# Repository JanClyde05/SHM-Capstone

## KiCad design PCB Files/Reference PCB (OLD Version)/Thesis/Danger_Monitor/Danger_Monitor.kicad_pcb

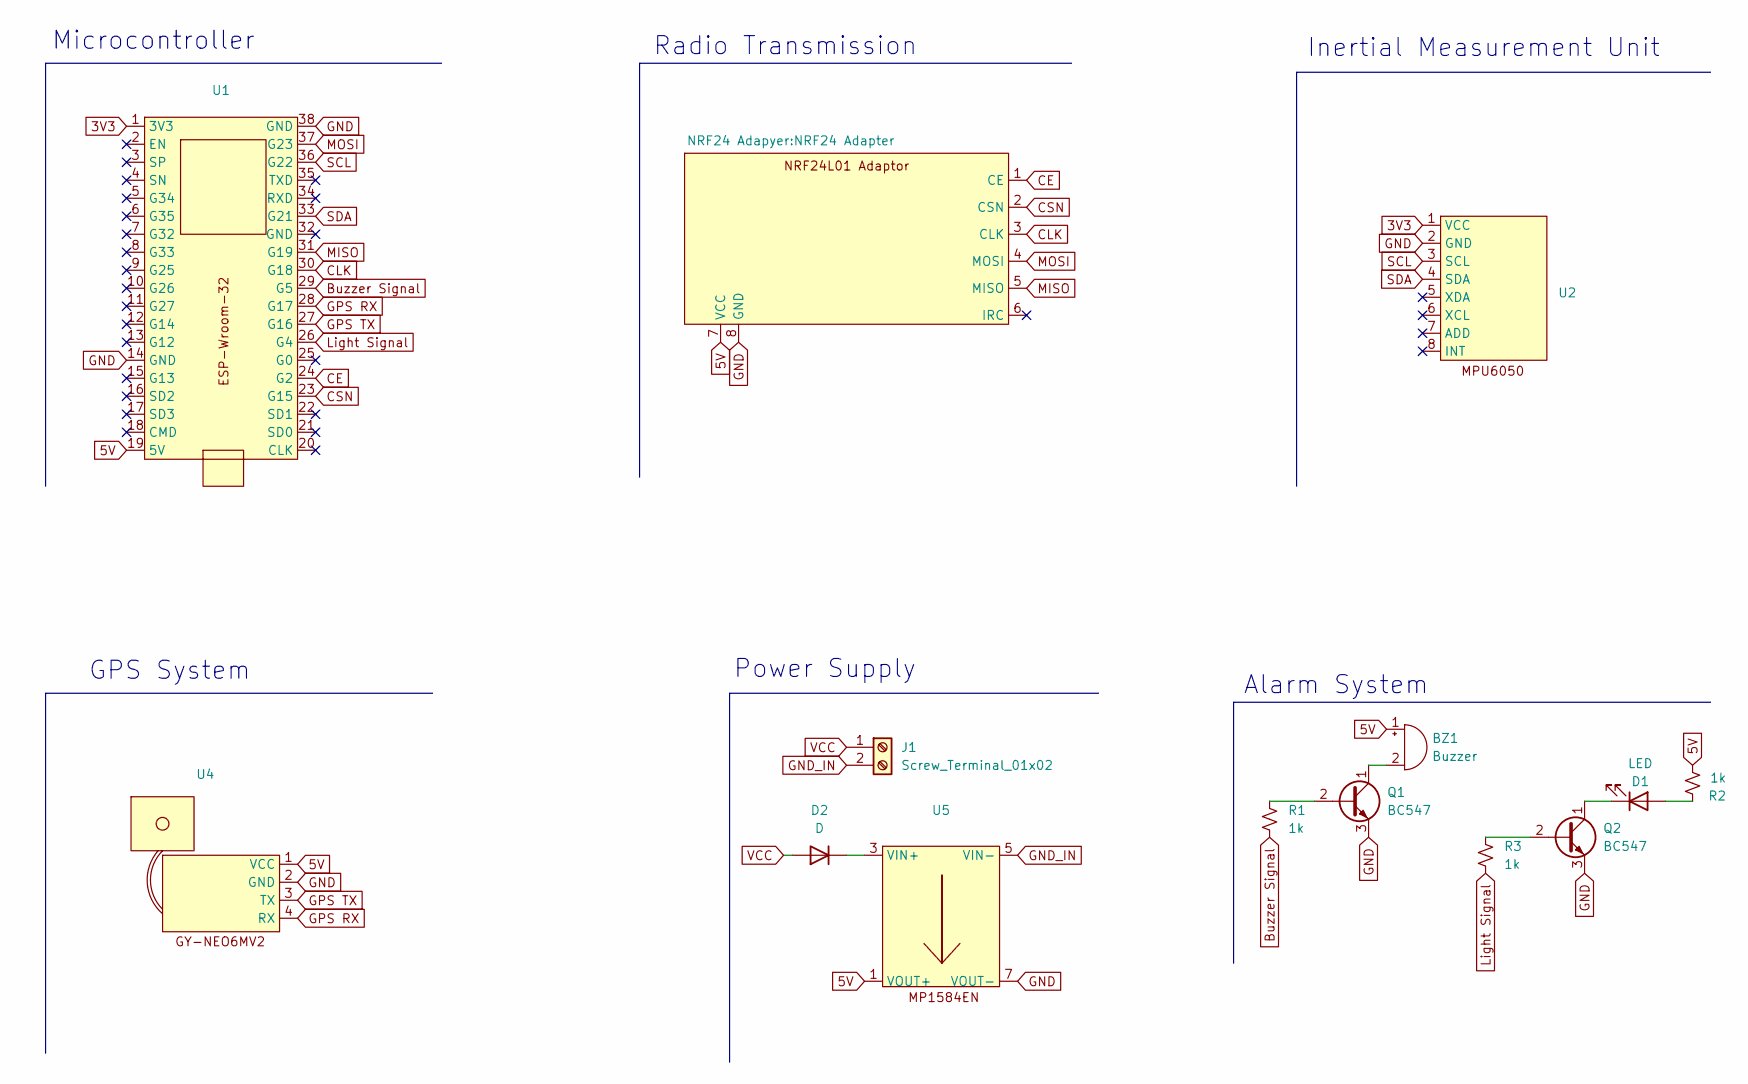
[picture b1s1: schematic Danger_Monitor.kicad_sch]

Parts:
BZ1: Buzzer; Buzzer_TDK_PS1240P02BT_D12.2mm_H6.5mm
D1: LED; LED_D5.0mm_Clear
D2: D; D_A-405_P10.16mm_Horizontal
J1: Screw_Terminal_01x02; Screw Terminal 2 Pin
Q1, Q2: BC547; TO-92_Inline
R1, R2, R3: 1k; R_Axial_DIN0207_L6.3mm_D2.5mm_P10.16mm_Horizontal
U1: ESP-WROOM-32
U2: MPU-6050
U3: NRF24 Adapter
U4: NEO7
U5: MP1584EN

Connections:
3V3: U1.1 (3V3), U2.1 (VCC)
5V: BZ1.1 (+), R2.2, U1.19 (5V), U3.7 (VCC), U4.1 (VCC), U5.1 (VOUT+), U5.2
Buzzer Signal: R1.2, U1.29 (G5)
CE: U1.24 (G2), U3.1 (CE)
CLK: U1.30 (G18), U3.3 (CLK)
CSN: U1.23 (G15), U3.2 (CSN)
GND: Q1.3 (E), Q2.3 (E), U1.14 (GND), U1.38 (GND), U2.2 (GND), U3.8 (GND), U4.2 (GND), U5.6, U5.7 (VOUT-)
GND_IN: J1.2, U5.5 (VIN-), U5.8
GPS RX: U1.28 (G17), U4.4 (RX)
GPS TX: U1.27 (G16), U4.3 (TX)
Light Signal: R3.2, U1.26 (G4)
MISO: U1.31 (G19), U3.5 (MISO)
MOSI: U1.37 (G23), U3.4 (MOSI)
unnamed: BZ1.2 (-), Q1.1 (C)
unnamed: D1.2 (A), R2.1
unnamed: D1.1 (K), Q2.1 (C)
unnamed: D2.1 (K), U5.3 (VIN+), U5.4
unnamed: Q1.2 (B), R1.1
unnamed: Q2.2 (B), R3.1
SCL: U1.36 (G22), U2.3 (SCL)
SDA: U1.33 (G21), U2.4 (SDA)
VCC: D2.2 (A), J1.1

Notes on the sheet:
Microcontroller
Inertial Measurement Unit
Radio Transmission
GPS System
Power Supply
Alarm System

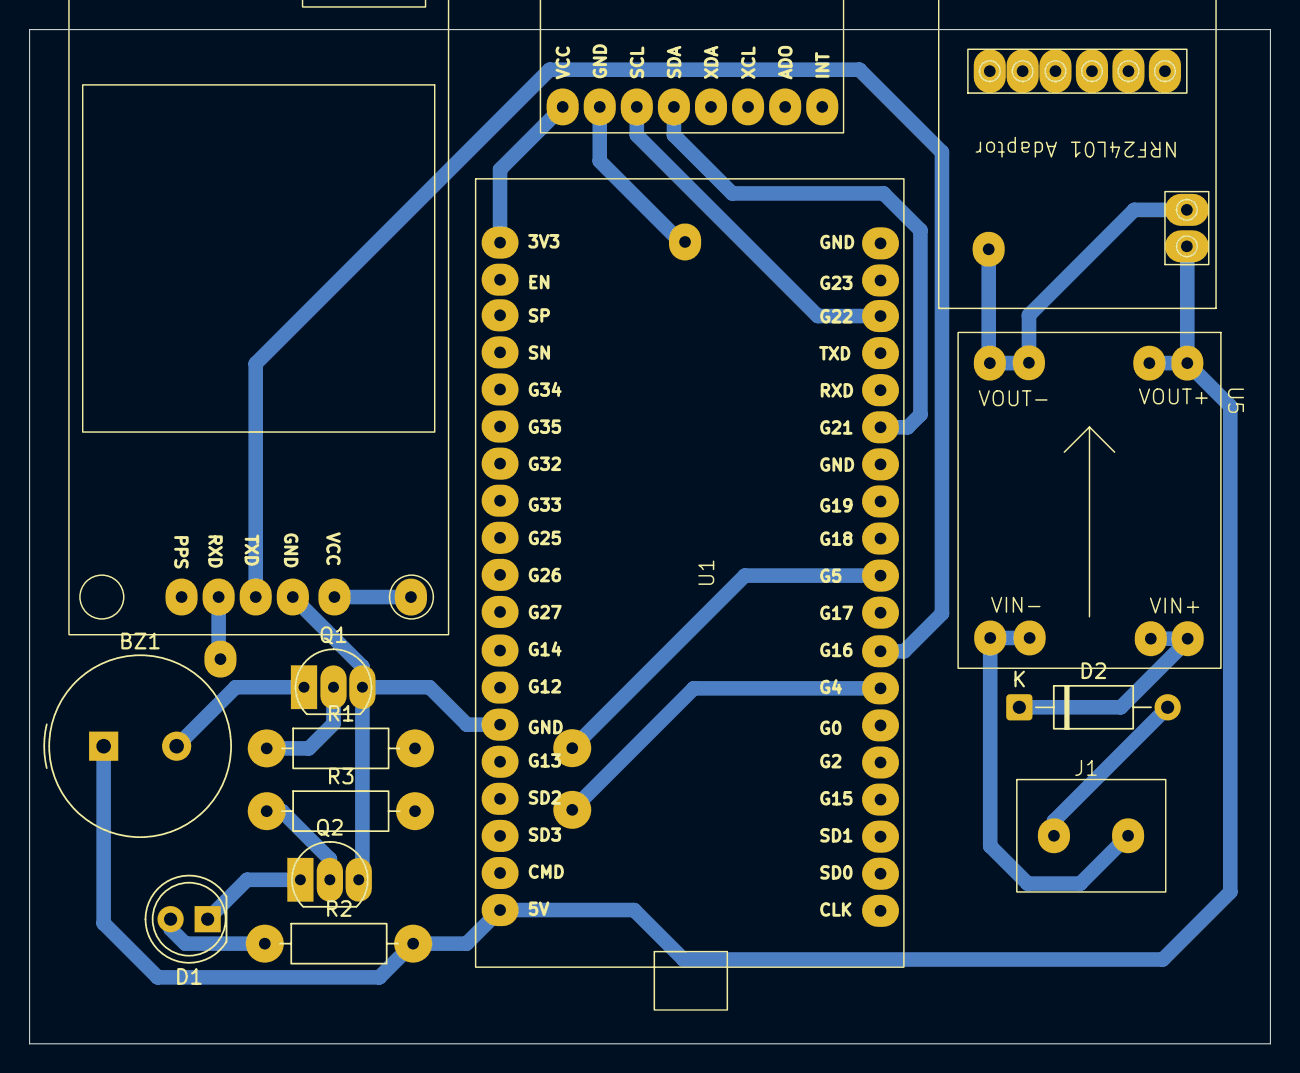
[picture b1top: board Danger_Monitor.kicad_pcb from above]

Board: 2 copper layers, 85.0 x 69.5 mm, 14 parts (0 on the bottom side), 22 nets.

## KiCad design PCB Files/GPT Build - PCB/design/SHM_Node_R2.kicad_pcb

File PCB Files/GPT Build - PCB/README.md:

# SHM frequency-acquisition hardware

## Engineering audit follow-up — 2026-10-29

Read [ENGINEERING_AUDIT_20261029.md](docs/ENGINEERING_AUDIT_20261029.md) and its [plan](docs/ENGINEERING_AUDIT_PLAN.md) before the next CAD edit. The deeper read-only audit found issues beyond configured ERC/DRC: USB A-contact transition imbalance (4 D+ versus 2 D−), missing explicit impedance stackup, no local capacitor directly on the ESD VBUS net, J2-to-U3 nominal body separation about 5.18 mm (5.13 mm conservative F.Fab box) against the TDK 6 mm insertion-component guidance, and unresolved thermal/probe-access qualification. Nominal antenna overhang is 0.10 mm with no recorded tolerance budget. These are engineering concerns, not observed prototype failures. Active PCB remains unchanged at SHA-256 `0ea352e982e6ccb87134d1d3dcef7bd3adb747efab5ba28b136cd1090f99540e`; the earlier configured CAD pass remains bounded evidence.

New evidence: `reports/engineering_audit/20261029/geometry.json`, `math.json`, and USB plane-screen SVG/PNG; reproducible tools `audit_engineering_geometry.py` and `audit_engineering_math.py`. Start with the report's ordered corrections and acceptance criteria. The audit did not change CAD, firmware or paper, and does not authorize fabrication.

The active KiCad design uses ESP32-S3-WROOM-1-N16R8, three bare MPU6050 ICs and one USB-C power/programming connection. It retains the user's **SHM_PCB_New 79.50 × 50.45 mm** silhouette.

Open [the KiCad project](design/SHM_Node_R2.kicad_pro), [schematic](design/SHM_Node_R2.kicad_sch), or [PCB](design/SHM_Node_R2.kicad_pcb). See [top preview](previews/active_pcb_3d_top.png) and [schematic PDF](previews/SHM_Node_R2_schematic.pdf).

**CAD checks pass; fabrication qualification remains open.** KiCad 10.0.6 ERC/DRC/connectivity/parity and the independent audit report zero findings under documented settings. [Exact evidence](reports/reference_corrected/validation_20261029T145905461959Z/manifest.json) records hashes, commands and ignored checks. PCB SHA-256: `0ea352e982e6ccb87134d1d3dcef7bd3adb747efab5ba28b136cd1090f99540e`.

Read [HANDOFF](docs/HANDOFF.md), [CONTINUATION_PLAN](docs/CONTINUATION_PLAN.md), [PROJECT_MAP](docs/PROJECT_MAP.md), [LAYOUT_REVIEW](docs/LAYOUT_REVIEW.md), [RESEARCH_LEDGER](docs/RESEARCH_LEDGER.md), [ERROR_LOG](docs/ERROR_LOG.md), [BOM](BOM.md) and [PROTOTYPE_BRINGUP](docs/PROTOTYPE_BRINGUP.md). The old wrong-outline board is preserved in `design/superseded_wrong_83mm_outline/`; staging history is in `design/reference_corrected/`.

Supplier stackup/USB impedance, remaining exact part selections, thermal/assembly/mounting review and all physical tests remain open. No bench or field performance is claimed. Arduino firmware and the approved paper are unchanged by this hardware continuation.

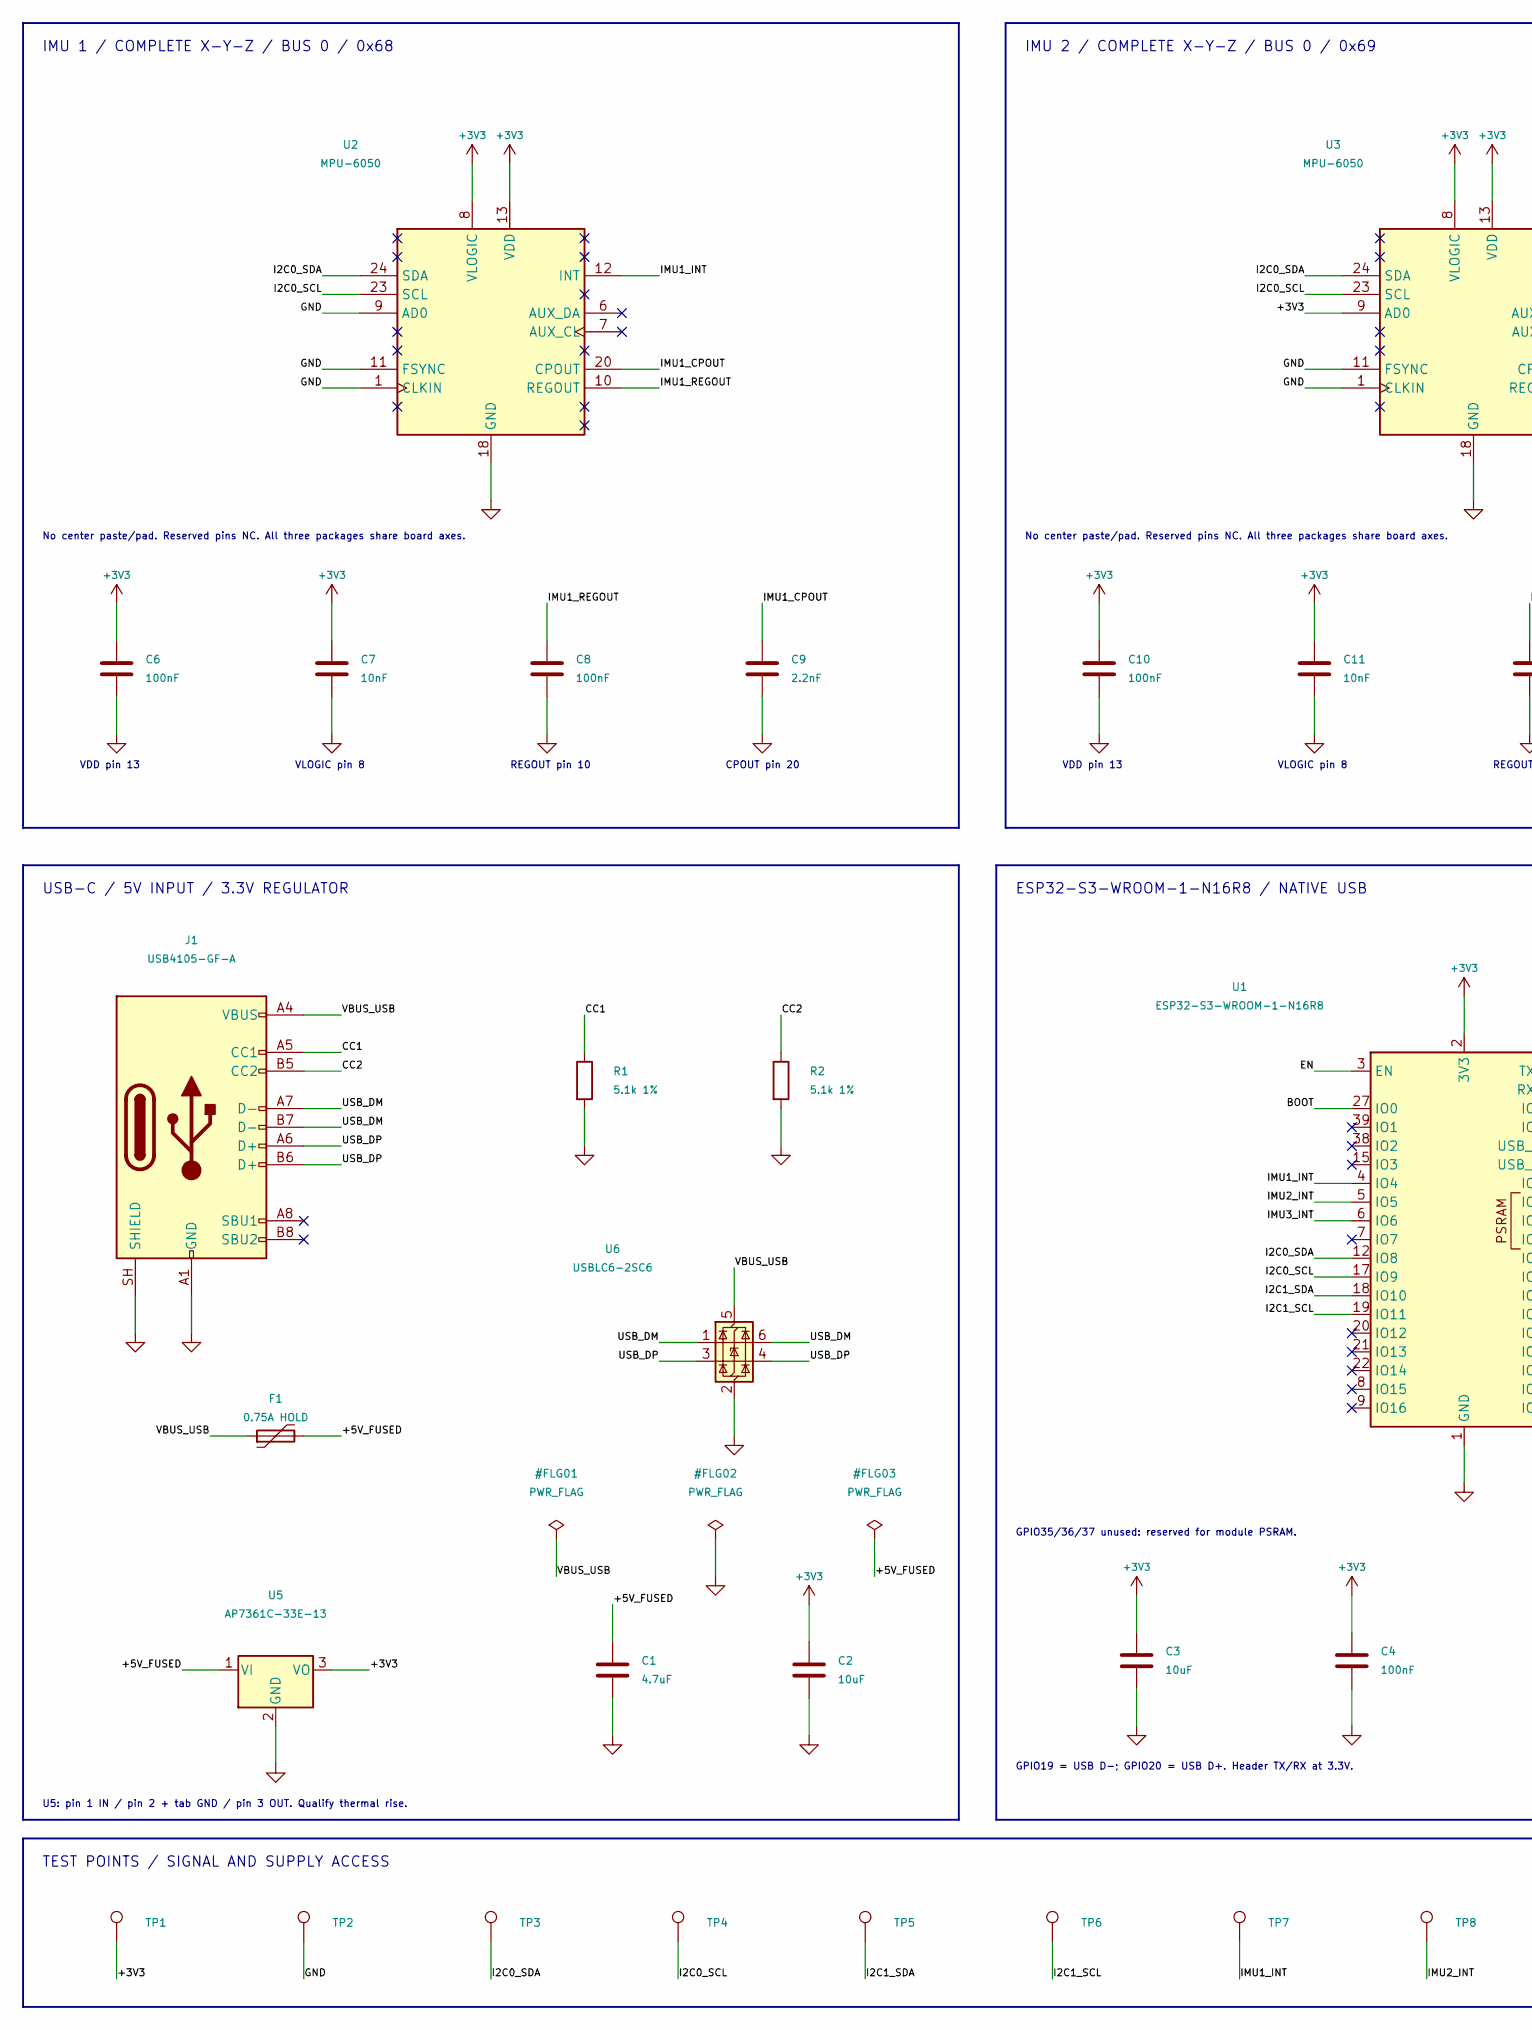
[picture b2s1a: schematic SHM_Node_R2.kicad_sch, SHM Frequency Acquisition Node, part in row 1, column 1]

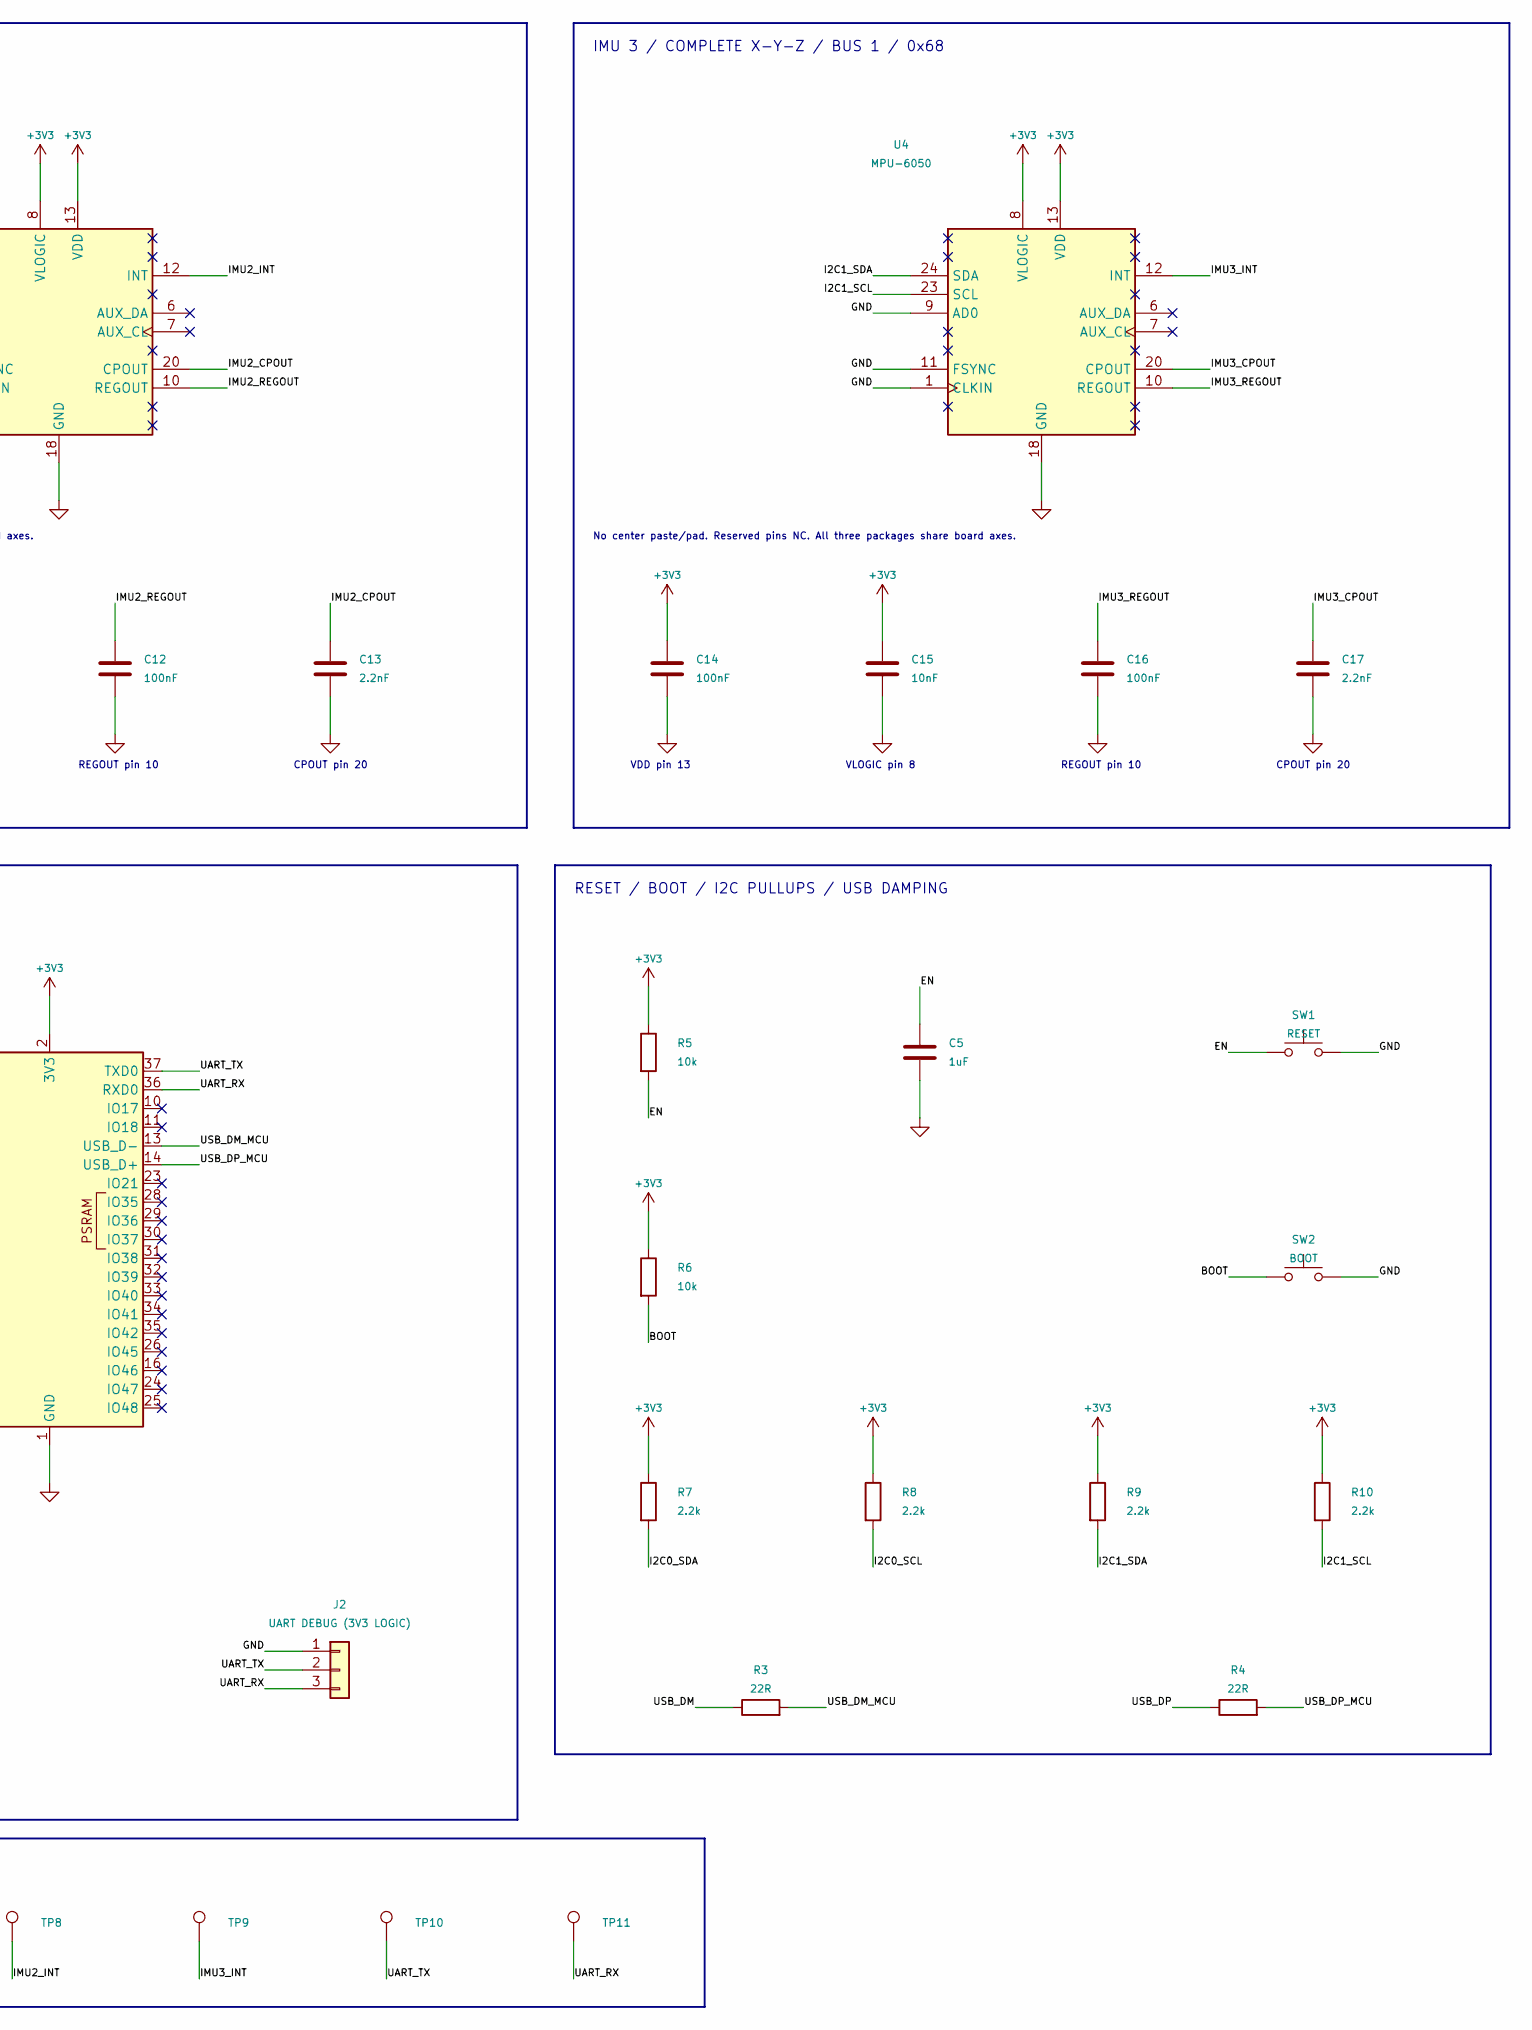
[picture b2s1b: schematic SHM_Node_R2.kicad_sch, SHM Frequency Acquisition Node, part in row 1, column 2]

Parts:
C1: 4.7uF; C_0805_2012Metric; Voltage 16V; Tolerance 10% or better
C2, C3: 10uF; C_0805_2012Metric; Voltage 16V; Tolerance 10% or better
C4, C6, C8, C10, C12, C14, C16: 100nF; C_0603_1608Metric; Voltage 25V; Tolerance 10% or better
C5: 1uF; C_0603_1608Metric; Voltage 25V; Tolerance 10% or better
C7, C11, C15: 10nF; C_0603_1608Metric; Voltage 25V; Tolerance 10% or better
C9, C13, C17: 2.2nF; C_0603_1608Metric; Voltage 50V; Tolerance 10% or better
F1: 0.75A HOLD; Fuse_1206_3216Metric; MPN 1206L075/16WR
J1: USB4105-GF-A; USB_C_Receptacle_GCT_USB4105-xx-A_16P_TopMnt_Horizontal
J2: UART DEBUG (3V3 LOGIC); PinHeader_1x03_P2.54mm_Vertical
R1, R2: 5.1k 1%; R_0603_1608Metric
R3, R4: 22R; R_0603_1608Metric
R5, R6: 10k; R_0603_1608Metric
R7, R8, R9, R10: 2.2k; R_0603_1608Metric
SW1: RESET; SW_SPST_TL3342
SW2: BOOT; SW_SPST_TL3342
TP1: +3V3; TestPoint_Pad_D1.0mm
TP2: GND; TestPoint_Pad_D1.0mm
TP3: I2C0_SDA; TestPoint_Pad_D1.0mm
TP4: I2C0_SCL; TestPoint_Pad_D1.0mm
TP5: I2C1_SDA; TestPoint_Pad_D1.0mm
TP6: I2C1_SCL; TestPoint_Pad_D1.0mm
TP7: IMU1_INT; TestPoint_Pad_D1.0mm
TP8: IMU2_INT; TestPoint_Pad_D1.0mm
TP9: IMU3_INT; TestPoint_Pad_D1.0mm
TP10: UART_TX; TestPoint_Pad_D1.0mm
TP11: UART_RX; TestPoint_Pad_D1.0mm
U1: ESP32-S3-WROOM-1-N16R8; ESP32-S3-WROOM-1_Overhang
U2, U3, U4: MPU-6050; MPU6050_QFN24_NoCenterPad
U5: AP7361C-33E-13; SOT-223-3_TabPin2
U6: USBLC6-2SC6; SOT-23-6

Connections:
+3V3: C2.1, C3.1, C4.1, C6.1, C7.1, C10.1, C11.1, C14.1, C15.1, R5.1, R6.1, R7.1, R8.1, R9.1, R10.1, TP1.1, U1.2 (3V3), U2.8 (VLOGIC), U2.13 (VDD), U3.8 (VLOGIC), U3.9 (AD0), U3.13 (VDD), U4.8 (VLOGIC), U4.13 (VDD), U5.3 (VO)
/+5V_FUSED: C1.1, F1.2, U5.1 (VI)
/BOOT: R6.2, SW2.1, U1.27 (IO0)
/CC1: J1.A5 (CC1), R1.1
/CC2: J1.B5 (CC2), R2.1
/EN: C5.1, R5.2, SW1.1, U1.3 (EN)
/I2C0_SCL: R8.2, TP4.1, U1.17 (IO9), U2.23 (SCL), U3.23 (SCL)
/I2C0_SDA: R7.2, TP3.1, U1.12 (IO8), U2.24 (SDA), U3.24 (SDA)
/I2C1_SCL: R10.2, TP6.1, U1.19 (IO11), U4.23 (SCL)
/I2C1_SDA: R9.2, TP5.1, U1.18 (IO10), U4.24 (SDA)
/IMU1_CPOUT: C9.1, U2.20 (CPOUT)
/IMU1_INT: TP7.1, U1.4 (IO4), U2.12 (INT)
/IMU1_REGOUT: C8.1, U2.10 (REGOUT)
/IMU2_CPOUT: C13.1, U3.20 (CPOUT)
/IMU2_INT: TP8.1, U1.5 (IO5), U3.12 (INT)
/IMU2_REGOUT: C12.1, U3.10 (REGOUT)
/IMU3_CPOUT: C17.1, U4.20 (CPOUT)
/IMU3_INT: TP9.1, U1.6 (IO6), U4.12 (INT)
/IMU3_REGOUT: C16.1, U4.10 (REGOUT)
/UART_RX: J2.3, TP11.1, U1.36 (RXD0)
/UART_TX: J2.2, TP10.1, U1.37 (TXD0)
/USB_DM: J1.A7 (D-), J1.B7 (D-), R3.1, U6.1 (I/O1), U6.6 (I/O1)
/USB_DM_MCU: R3.2, U1.13 (USB_D-)
/USB_DP: J1.A6 (D+), J1.B6 (D+), R4.1, U6.3 (I/O2), U6.4 (I/O2)
/USB_DP_MCU: R4.2, U1.14 (USB_D+)
/VBUS_USB: F1.1, J1.A4 (VBUS), J1.A9 (VBUS), J1.B4 (VBUS), J1.B9 (VBUS), U6.5 (VBUS)
GND: C1.2, C2.2, C3.2, C4.2, C5.2, C6.2, C7.2, C8.2, C9.2, C10.2, C11.2, C12.2, C13.2, C14.2, C15.2, C16.2, C17.2, J1.A1 (GND), J1.A12 (GND), J1.B1 (GND), J1.B12 (GND), J1.SH (SHIELD), J2.1, R1.2, R2.2, SW1.2, SW2.2, TP2.1, U1.1 (GND), U1.40 (GND), U1.41 (GND), U2.1 (CLKIN), U2.9 (AD0), U2.11 (FSYNC), U2.18 (GND), U3.1 (CLKIN), U3.11 (FSYNC), U3.18 (GND), U4.1 (CLKIN), U4.9 (AD0), U4.11 (FSYNC), U4.18 (GND), U5.2 (GND), U6.2 (GND)

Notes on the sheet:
IMU 1 / COMPLETE X-Y-Z / BUS 0 / 0x68
VDD pin 13
VLOGIC pin 8
REGOUT pin 10
CPOUT pin 20
No center paste/pad. Reserved pins NC. All three packages share board axes.
IMU 2 / COMPLETE X-Y-Z / BUS 0 / 0x69
IMU 3 / COMPLETE X-Y-Z / BUS 1 / 0x68
USB-C / 5V INPUT / 3.3V REGULATOR
U5: pin 1 IN / pin 2 + tab GND / pin 3 OUT. Qualify thermal rise.
ESP32-S3-WROOM-1-N16R8 / NATIVE USB
GPIO35/36/37 unused: reserved for module PSRAM.
GPIO19 = USB D-; GPIO20 = USB D+. Header TX/RX at 3.3V.
RESET / BOOT / I2C PULLUPS / USB DAMPING
TEST POINTS / SIGNAL AND SUPPLY ACCESS

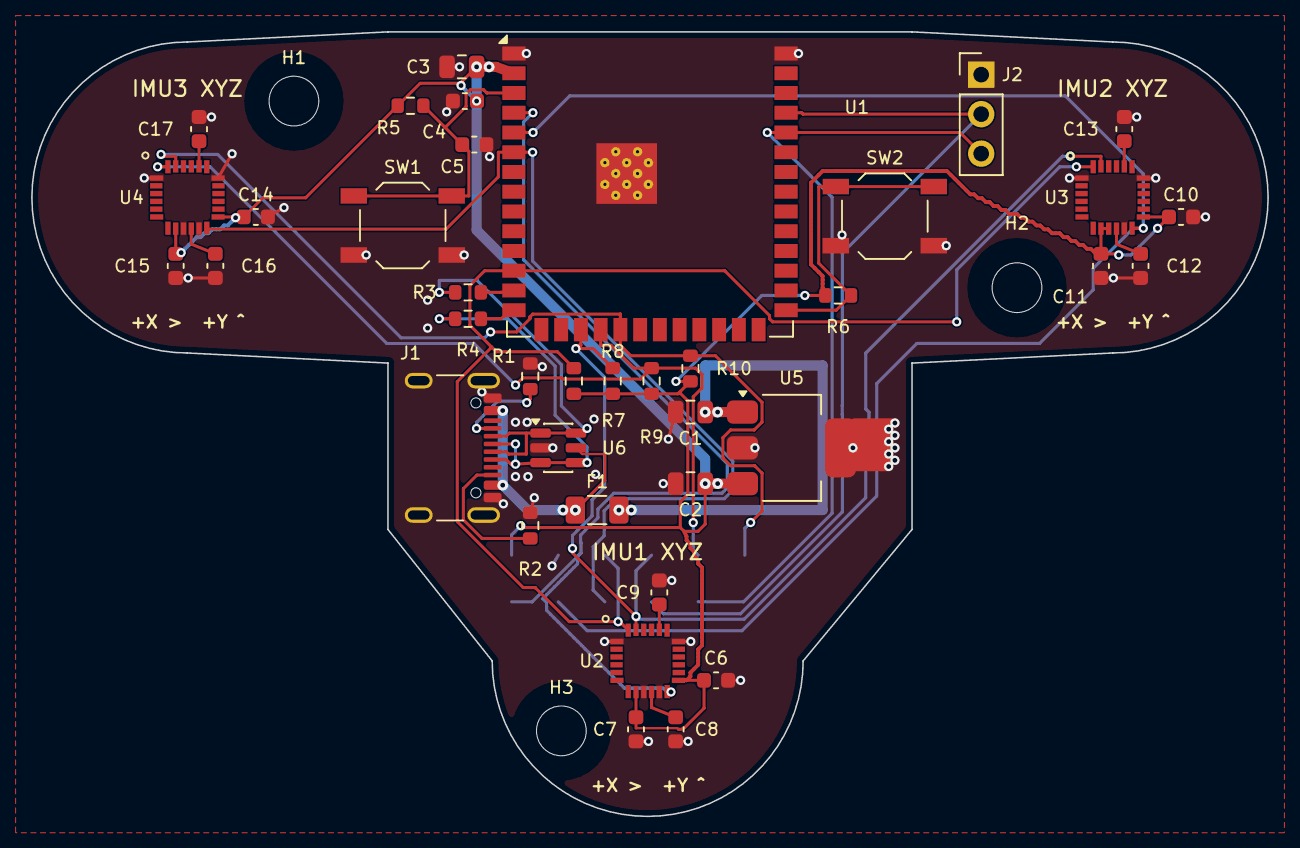
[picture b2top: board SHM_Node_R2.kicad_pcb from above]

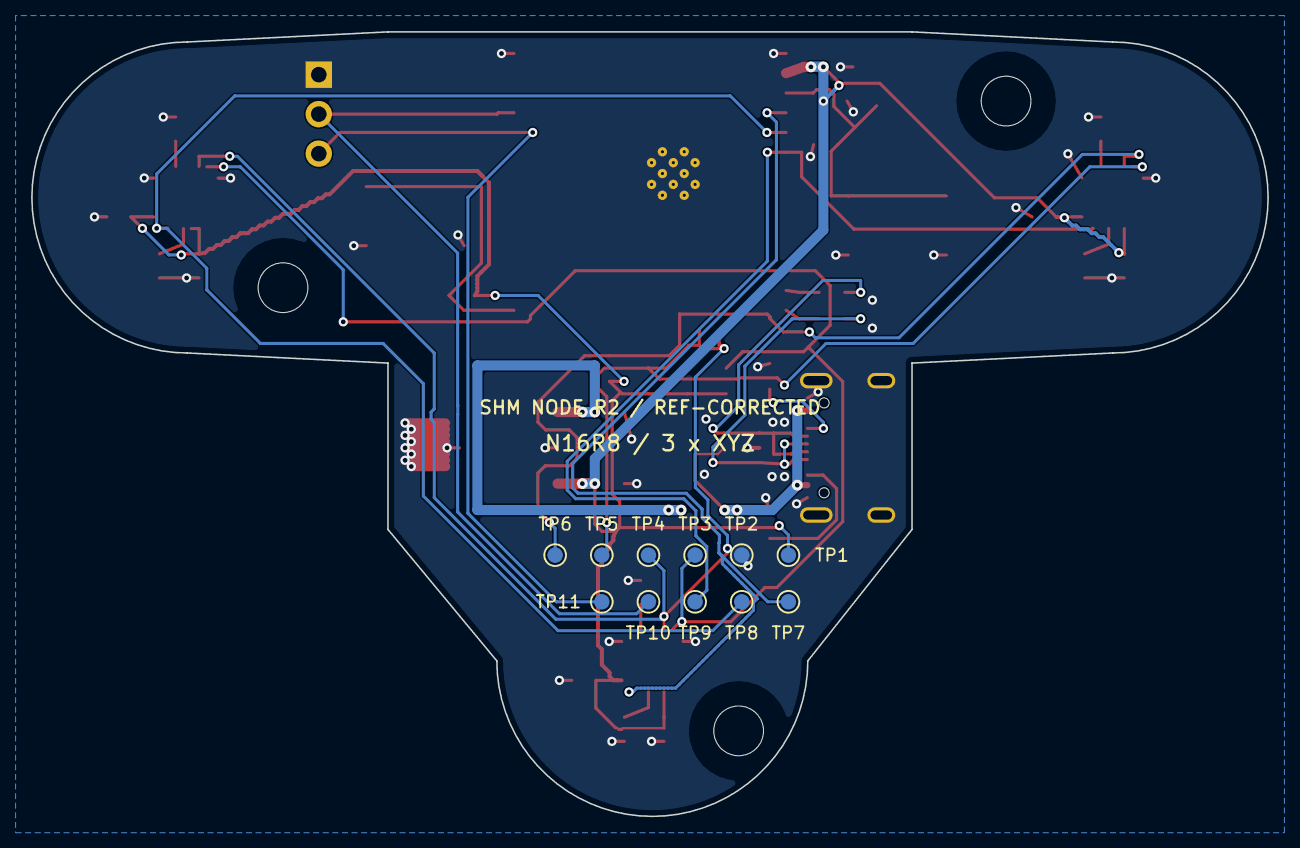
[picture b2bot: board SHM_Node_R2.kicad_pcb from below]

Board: 4 copper layers, 79.5 x 50.5 mm, 52 parts (11 on the bottom side), 27 nets.

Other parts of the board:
H1, H2, H3: M3 NPTH; MountingHole_3.2mm_M3

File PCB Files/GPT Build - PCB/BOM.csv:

References,Quantity,Value_or_function,Manufacturer,MPN,Footprint,Requirements,Status,Source_URL,Notes
"U2, U3, U4",3,MPU-6050,TDK InvenSense,MPU-6050,SHM_Local:MPU6050_QFN24_NoCenterPad,,Selected exact MPN; availability not checked,https://d17t6iyxenbwp1.cloudfront.net/s3fs-public/2026-04/ps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,Bare QFN24; no center-pad solder or paste. Source authentic parts; identical placement orientation.
"C6, C8, C10, C12, C14, C16, C4",7,100nF,,,Capacitor_SMD:C_0603_1608Metric,Voltage: 25V; Dielectric: X7R; Tolerance: 10% or better,Specification only; MPN not selected,,Verify effective capacitance at operating DC bias and package fit before ordering.
"C7, C11, C15",3,10nF,,,Capacitor_SMD:C_0603_1608Metric,Voltage: 25V; Dielectric: X7R; Tolerance: 10% or better,Specification only; MPN not selected,,Verify effective capacitance at operating DC bias and package fit before ordering.
"C9, C13, C17",3,2.2nF,,,Capacitor_SMD:C_0603_1608Metric,Voltage: 50V; Dielectric: X7R; Tolerance: 10% or better,Specification only; MPN not selected,,"Charge-pump capacitor: 2.2nF X7R 50V, tolerance 10% or better; retain this voltage rating."
J1,1,USB4105-GF-A,GCT,USB4105-GF-A,Connector_USB:USB_C_Receptacle_GCT_USB4105-xx-A_16P_TopMnt_Horizontal,,Selected exact MPN; availability not checked,https://gct.co/files/drawings/usb4105.pdf,GF gold flash; A tape/reel; standard0.95mm shell stakes. Match manufacturer land pattern.
"R1, R2",2,5.1k 1%,,,Resistor_SMD:R_0603_1608Metric,0603; proposed 1% tolerance and >=0.1W; verify selected manufacturer ratings,Specification only; MPN not selected,,CC resistors R1/R2 explicitly require 1% in circuit spec.
U6,1,USBLC6-2SC6,STMicroelectronics,USBLC6-2SC6,Package_TO_SOT_SMD:SOT-23-6,,Selected exact MPN; availability not checked,https://www.st.com/resource/en/datasheet/usblc6-2.pdf,"SOT23-6 SC6 variant; pins2GND,5VBUS; I/O pairs1/6 and3/4."
F1,1,0.75A HOLD,Littelfuse,1206L075/16WR,Fuse:Fuse_1206_3216Metric,,Selected exact MPN; availability not checked,https://www.littelfuse.com/assetdocs/littelfuse-ptc-1206l-da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,0.75A hold at20C; temperature derating and voltage drop require validation. WR suffix corrected after audit.
U5,1,AP7361C-33E-13,Diodes Incorporated,AP7361C-33E-13,Package_TO_SOT_SMD:SOT-223-3_TabPin2,,Selected exact MPN; availability not checked,https://www.diodes.com/datasheet/download/AP7361C.pdf,SOT223 E pinout IN1/GND2+tab/OUT3; not1117/ER pinout. Thermal validation required.
C1,1,4.7uF,,,Capacitor_SMD:C_0805_2012Metric,Voltage: 16V; Dielectric: X7R; Tolerance: 10% or better,Specification only; MPN not selected,,Verify effective capacitance at operating DC bias and package fit before ordering.
"C2, C3",2,10uF,,,Capacitor_SMD:C_0805_2012Metric,Voltage: 16V; Dielectric: X7R; Tolerance: 10% or better,Specification only; MPN not selected,,Verify effective capacitance at operating DC bias and package fit before ordering.
U1,1,ESP32-S3-WROOM-1-N16R8,Espressif Systems,ESP32-S3-WROOM-1-N16R8,SHM_Local:ESP32-S3-WROOM-1_Overhang,,Selected exact MPN; availability not checked,https://www.espressif.com/sites/default/files/documentation/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,N16R8 variant required: 16MB flash/8MB PSRAM; local overhang footprint changes graphics only.
J2,1,UART DEBUG 3V3,,,Connector_PinHeader_2.54mm:PinHeader_1x03_P2.54mm_Vertical,,Specification only; MPN not selected,,"1x3, 2.54mm vertical header; pins GND/TX/RX, 3.3V logic; no supply pin."
"R5, R6",2,10k,,,Resistor_SMD:R_0603_1608Metric,0603; proposed 1% tolerance and >=0.1W; verify selected manufacturer ratings,Specification only; MPN not selected,,
C5,1,1uF,,,Capacitor_SMD:C_0603_1608Metric,Voltage: 25V; Dielectric: X7R; Tolerance: 10% or better,Specification only; MPN not selected,,Verify effective capacitance at operating DC bias and package fit before ordering.
"SW1, SW2",2,"Momentary pushbutton, normally open",,,Button_Switch_SMD:SW_SPST_TL3342,,Specification only; MPN not selected,,"TL3342 footprint family only; exact order suffix, actuator height and manufacturer drawing remain unconfirmed."
"R7, R8, R9, R10",4,2.2k,,,Resistor_SMD:R_0603_1608Metric,0603; proposed 1% tolerance and >=0.1W; verify selected manufacturer ratings,Specification only; MPN not selected,,
"R3, R4",2,22R,,,Resistor_SMD:R_0603_1608Metric,0603; proposed 1% tolerance and >=0.1W; verify selected manufacturer ratings,Specification only; MPN not selected,,
"TP1, TP2, TP3, TP4, TP5, TP6, TP7, TP8, TP9, TP10, TP11",11,PCB test pad,,,TestPoint:TestPoint_Pad_D1.0mm,,PCB feature; do not purchase,,1.0mm exposed test pad; no separate component.

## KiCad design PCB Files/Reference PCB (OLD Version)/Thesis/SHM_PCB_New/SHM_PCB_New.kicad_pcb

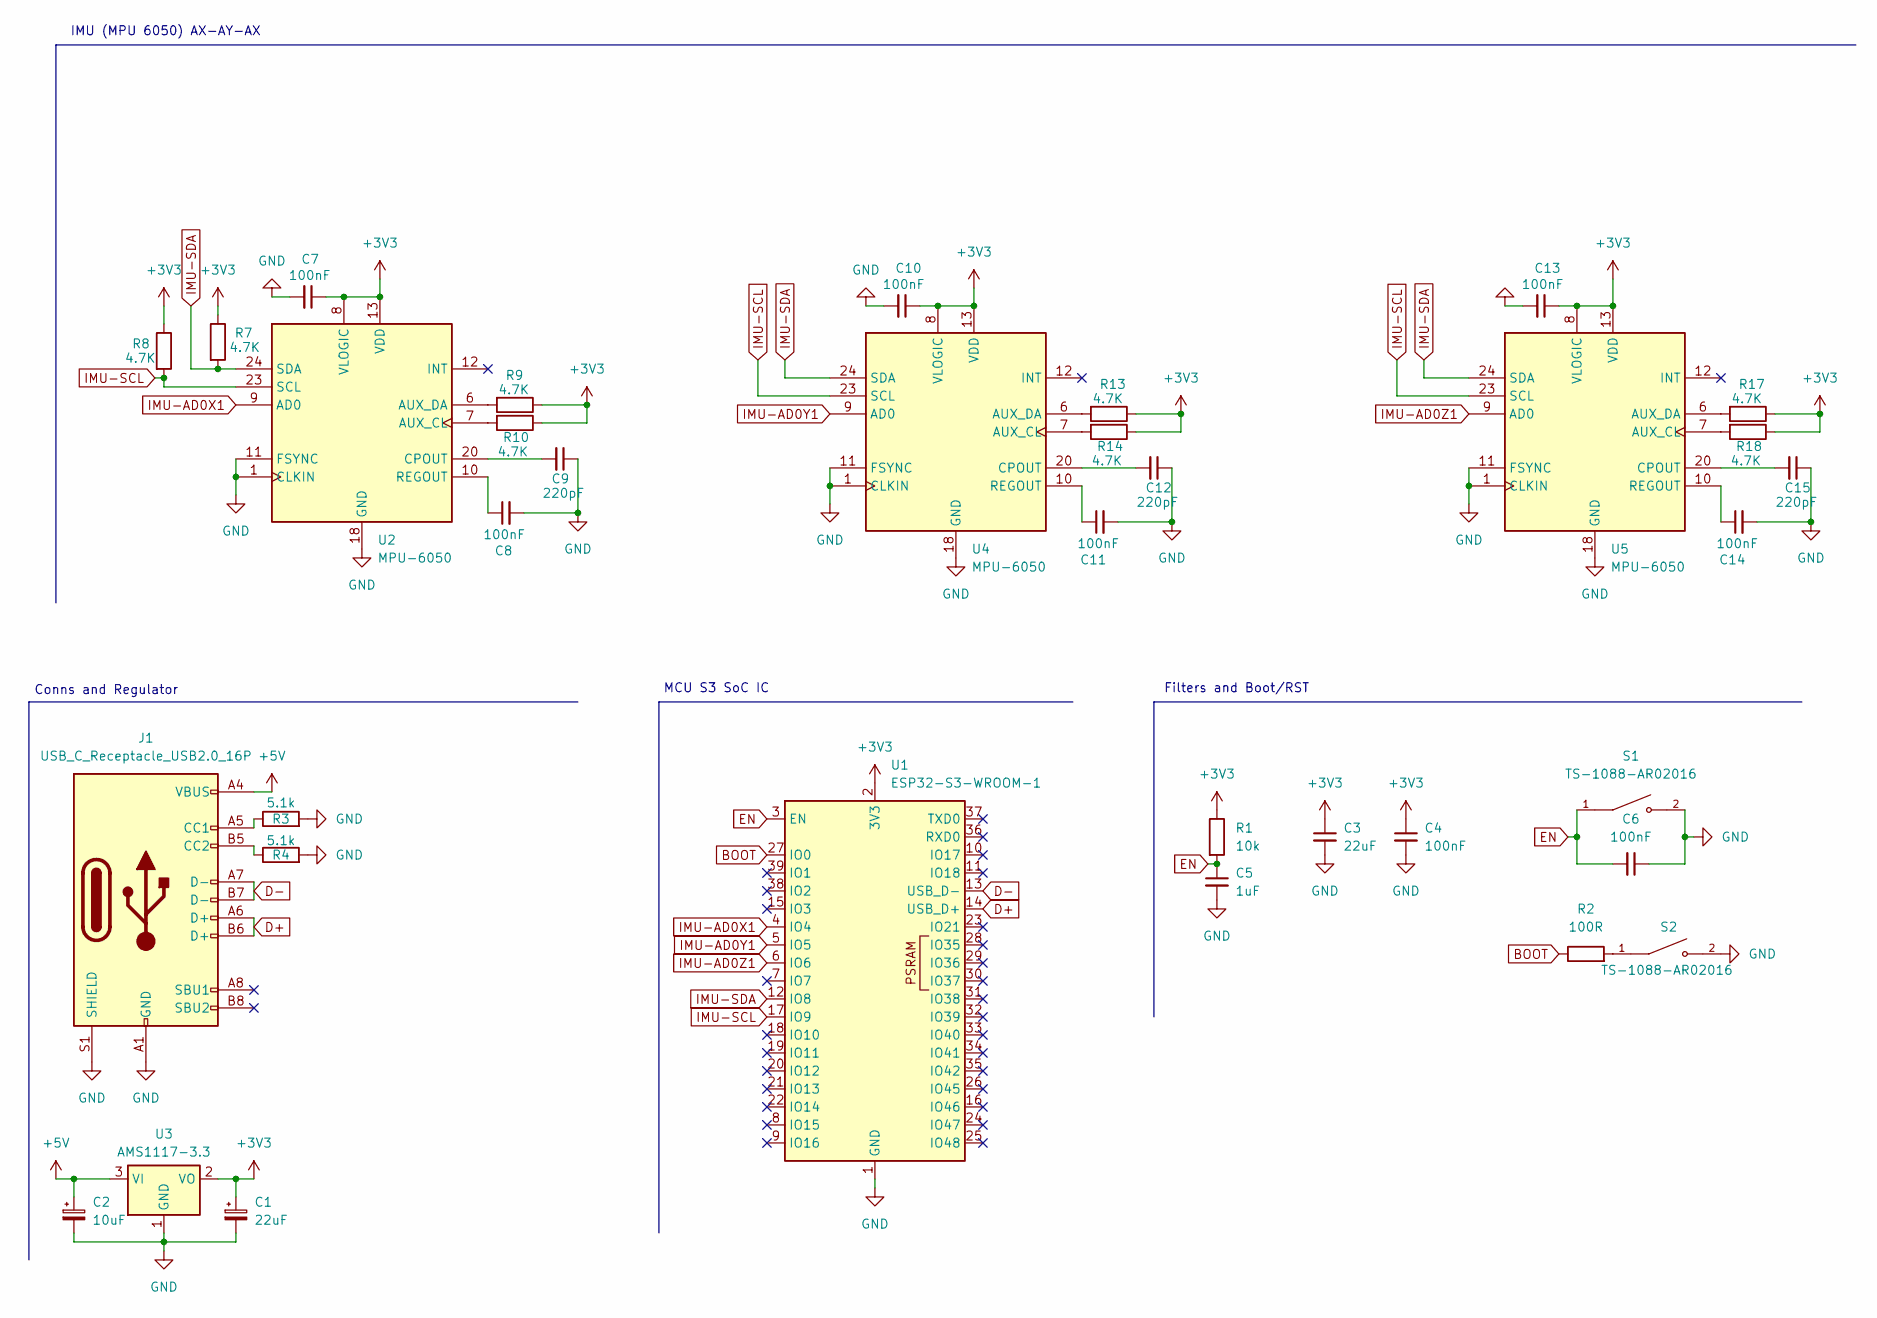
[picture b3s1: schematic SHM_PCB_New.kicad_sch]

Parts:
C1: 22uF; CP_EIA-2012-15_AVX-P_HandSolder
C2: 10uF; CP_EIA-2012-15_AVX-P_HandSolder
C3: 22uF; C_0805_2012Metric_Pad1.18x1.45mm_HandSolder
C4, C6, C7, C8, C10, C11, C13, C14: 100nF; C_0805_2012Metric_Pad1.18x1.45mm_HandSolder
C5: 1uF; C_0805_2012Metric_Pad1.18x1.45mm_HandSolder
C9, C12, C15: 220pF; C_0805_2012Metric_Pad1.18x1.45mm_HandSolder
J1: USB_C_Receptacle_USB2.0_16P; USB_C_Receptacle_GCT_USB4105-xx-A_16P_TopMnt_Horizontal
R1: 10k; R_0805_2012Metric_Pad1.20x1.40mm_HandSolder
R2: 100R; R_0805_2012Metric_Pad1.20x1.40mm_HandSolder
R3, R4: 5.1k; R_0805_2012Metric_Pad1.20x1.40mm_HandSolder
R7, R8, R9, R10, R13, R14, R17, R18: 4.7K; R_0805_2012Metric_Pad1.20x1.40mm_HandSolder
S1, S2: TS-1088-AR02016; SW_TS-1088-AR02016; PARTREV N/A
U1: ESP32-S3-WROOM-1
U2, U4, U5: MPU-6050; InvenSense_QFN-24_4x4mm_P0.5mm
U3: AMS1117-3.3; SOT-223-3_TabPin2

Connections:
+3V3: C1.1, C3.1, C4.1, C7.1, C10.1, C13.1, R1.1, R7.1, R8.1, R9.1, R10.1, R13.1, R14.1, R17.1, R18.1, U1.2 (3V3), U2.8 (VLOGIC), U2.13 (VDD), U3.2 (VO), U4.8 (VLOGIC), U4.13 (VDD), U5.8 (VLOGIC), U5.13 (VDD)
+5V: C2.1, J1.A4 (VBUS), J1.A9 (VBUS), J1.B4 (VBUS), J1.B9 (VBUS), U3.3 (VI)
BOOT: R2.1, U1.27 (IO0)
D+: J1.A6 (D+), J1.B6 (D+), U1.14 (USB_D+)
D-: J1.A7 (D-), J1.B7 (D-), U1.13 (USB_D-)
EN: C5.1, C6.2, R1.2, S1.1, U1.3 (EN)
GND: C1.2, C2.2, C3.2, C4.2, C5.2, C6.1, C7.2, C8.2, C9.1, C10.2, C11.2, C12.1, C13.2, C14.2, C15.1, J1.A1 (GND), J1.A12 (GND), J1.B1 (GND), J1.B12 (GND), J1.S1 (SHIELD), R3.2, R4.2, S1.2, S2.2, U1.1 (GND), U1.40 (GND), U1.41 (GND), U2.1 (CLKIN), U2.11 (FSYNC), U2.18 (GND), U3.1 (GND), U4.1 (CLKIN), U4.11 (FSYNC), U4.18 (GND), U5.1 (CLKIN), U5.11 (FSYNC), U5.18 (GND)
IMU-AD0X1: U1.4 (IO4), U2.9 (AD0)
IMU-AD0Y1: U1.5 (IO5), U4.9 (AD0)
IMU-AD0Z1: U1.6 (IO6), U5.9 (AD0)
IMU-SCL: R8.2, U1.17 (IO9), U2.23 (SCL), U4.23 (SCL), U5.23 (SCL)
IMU-SDA: R7.2, U1.12 (IO8), U2.24 (SDA), U4.24 (SDA), U5.24 (SDA)
unnamed: J1.A5 (CC1), R3.1
unnamed: J1.B5 (CC2), R4.1
unnamed: R2.2, S2.1
unnamed: R10.2, U2.7 (AUX_CL)
unnamed: R9.2, U2.6 (AUX_DA)
unnamed: C9.2, U2.20 (CPOUT)
unnamed: C8.1, U2.10 (REGOUT)
unnamed: R14.2, U4.7 (AUX_CL)
unnamed: R13.2, U4.6 (AUX_DA)
unnamed: C12.2, U4.20 (CPOUT)
unnamed: C11.1, U4.10 (REGOUT)
unnamed: R18.2, U5.7 (AUX_CL)
unnamed: R17.2, U5.6 (AUX_DA)
unnamed: C15.2, U5.20 (CPOUT)
unnamed: C14.1, U5.10 (REGOUT)

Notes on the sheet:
Conns and Regulator
Filters and Boot/RST
IMU (MPU 6050) AX-AY-AX
MCU S3 SoC IC
